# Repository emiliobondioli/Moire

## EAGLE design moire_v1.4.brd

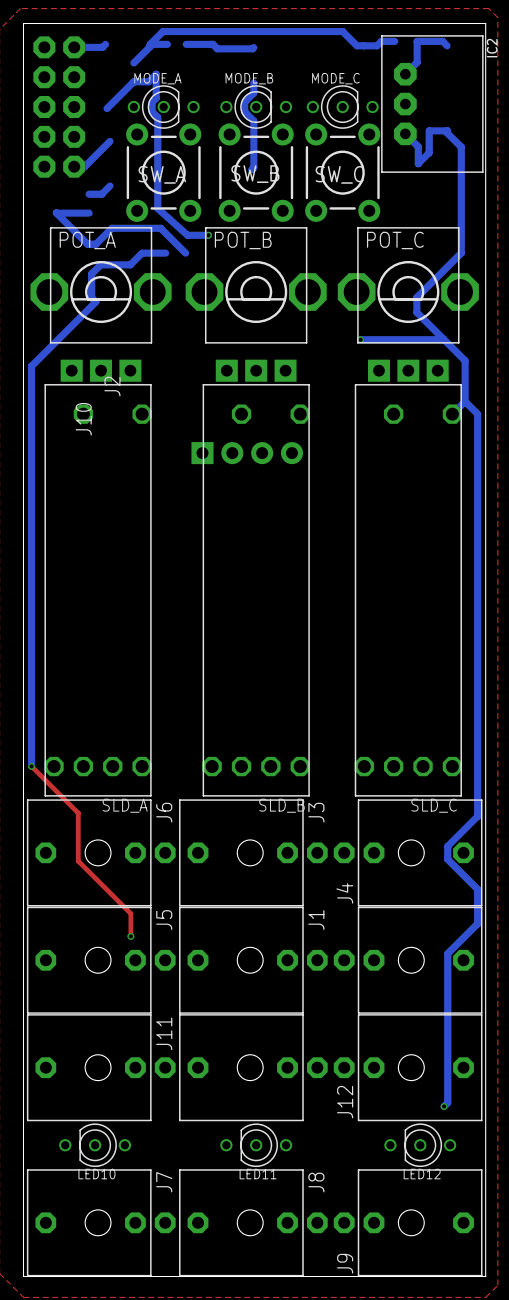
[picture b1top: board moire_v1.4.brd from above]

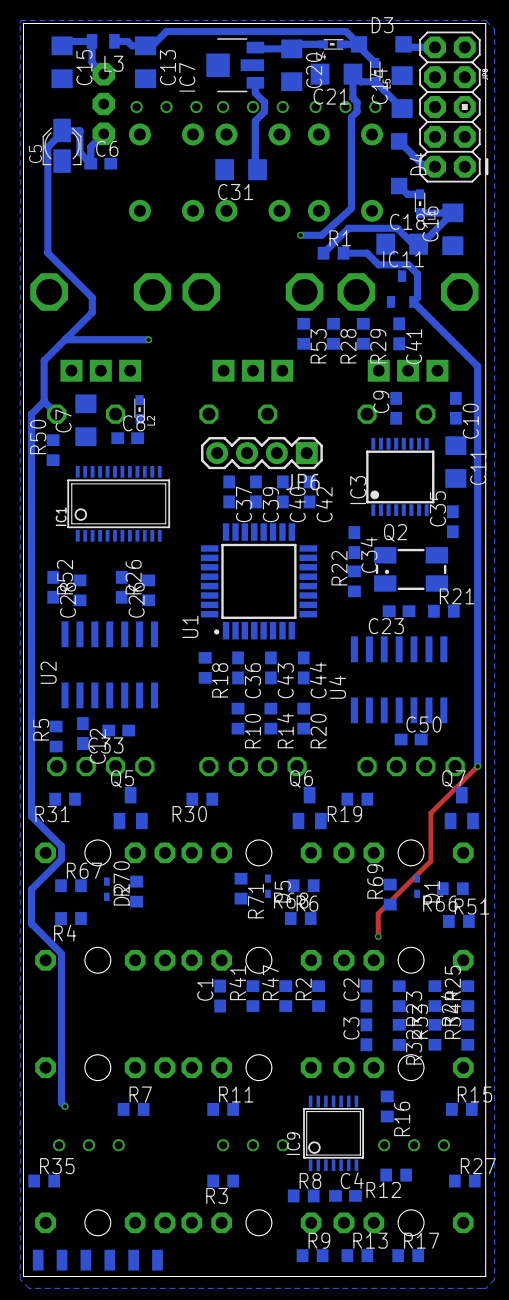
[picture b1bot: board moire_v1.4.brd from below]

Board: 2 copper layers, 39.4 x 106.7 mm, 135 parts (107 on the bottom side), 102 nets.

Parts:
C1, C2, C3: 100p; C0603
C4, C6, C8, C9, C10, C23, C33, C36, C37, C39, C43, C50: 100n; C0603
C5: 10u; PANASONIC_A
C7, C11, C13, C14, C15, C16, C18, C20, C21, C31: 22u; C1206
C12, C26, C28: 2.2n; C0603
C34, C35: 20p; C0603
C40, C41, C42, C44: 1u; C0603
D1, D2, D5: 1N4148; SOD523
D3, D4: 1N5819HW; SOD123
IC1: TLC59281DBQ; TSSOP24_0635
IC2: R-78E3.3-0.5; WE78
IC3: 4051PW; TSSOP16_065
IC7: LD2981ABU33; SOT89
IC9: LM324PW; TSSOP14_065
IC11: LM4040B25; DBZ_R-PDSO-G3
J1, J2, J3, J4, J5, J6, J7, J8, J9, J10, J11, J12: PJ301_THONKICONN6; WQP_PJ_301M6
JP6: 1X04
JP8: M05X2PTH; 2X5-PTH
L1, L2, L4, L5: 0603
L3: 33u; L2012C
LED10, LED11, LED12: SSL-LX3059IGW-CA; LED-BICOLOR-THROUGHHOLE-LUMEX
MODE_A: SSL-LX3059IGW-CA; LED-BICOLOR-THROUGHHOLE-LUMEX
MODE_B: SSL-LX3059IGW-CA; LED-BICOLOR-THROUGHHOLE-LUMEX
MODE_C: SSL-LX3059IGW-CA; LED-BICOLOR-THROUGHHOLE-LUMEX
POT_A: 10kB; ALPS_POT_VERTICAL
POT_B: 10kB; ALPS_POT_VERTICAL
POT_C: 10kB; ALPS_POT_VERTICAL
Q2: 8MHz; CTS406
Q5, Q6, Q7: MMBT3904; SOT23-BEC
R1, R10, R14, R18, R20, R50: 10k; R0603
R2, R25, R28, R29, R34, R53: 30k; R0603
R3, R7, R11, R15, R27, R35: 1.0k; R0603
R4, R6, R8, R12, R16, R23, R32, R41, R51, R66, R67, R68, R69, R70, R71: 100k; R0603
R5, R24, R26, R33, R47, R52: 20k; R0603
R9, R13, R17: 69.8k; R0603
R19, R30, R31: 15k; R0603
R21, R22: 100; R0603
SLD_A: 20kB; BOURNS_SLIDER
SLD_B: 20kB; BOURNS_SLIDER
SLD_C: 20kB; BOURNS_SLIDER
SW_A: TACTILE-PTH
SW_B: TACTILE-PTH
SW_C: TACTILE-PTH
U1: STM32F303K8T6; QFP80P900X900X160-32N
U2: MCP6004; SO14
U4: TL074; SO14
U$1: 1X6-SMD-TESTPAD; 6X1-SMD-TESTPAD

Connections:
+3V3: C5.+, C6.1, C37.1, C39.1, C40.1, C42.1, IC2.3, L2.2, LED10.A, LED11.A, LED12.A, MODE_A.A, MODE_B.A, MODE_C.A, R18.1, SLD_A.B, SLD_B.B, SLD_C.B, U1.1, U1.17, U$1.3
+3V3_A: C9.1, C10.1, C11.1, C31.1, C33.1, C43.1, C44.1, IC3.16, IC7.1, POT_A.P$1, POT_B.P$1, POT_C.P$1, SLD_A.3, SLD_B.3, SLD_C.3, U1.5, U2.4, U$1.4
+12V: D3.A, JP8.9, JP8.10
-12V: D4.C, JP8.1, JP8.2
ADC_TIME_SHAPE: IC3.3, U1.9
AREF_-2.5: C41.1, IC11.2, R1.2, R2.2, R25.2, R28.2, R29.2, R34.2, R53.2, U$1.5
A_ADC: R47.2, U1.10
A_CV: C12.2, R5.1, U1.6, U2.1
A_GATE: R10.2, U1.20
A_TRIG: Q5.C, U1.25
A_TRIG_IN: J4.P3, R67.1
B_ADC: R24.2, U1.11
B_CV: C26.2, R26.1, U1.7, U2.8
B_CV_IN: J1.P3, R6.2
B_GATE: R14.2, U1.21
B_TRIG: Q6.C, U1.14
B_TRIG_IN: J3.P3, R68.1
C_ADC: R33.2, U1.12
C_CV: C28.2, R52.1, U1.8, U2.14
C_GATE: R20.2, U1.22
C_TRIG: Q7.C, U1.15
C_TRIG_IN: J6.P3, R66.1
GND: C4.2, C5.-, C6.2, C7.2, C8.2, C9.2, C10.2, C11.2, C13.2, C14.2, C15.2, C16.1, C18.1, C20.2, C21.2, C23.1, C31.2, C33.2, C34.1, C35.1, C36.2, C37.2, C39.2, C40.2, C41.2, C42.2, C43.2, C44.2, C50.2, D1.A, D2.A, D5.A, IC1.1, IC1.21, IC2.2, IC3.6, IC3.7, IC3.8, IC7.2, IC9.11, IC9.12, IC11.1, J1.P1, J1.P2, J2.P1, J2.P2, J3.P1, J3.P2, J4.P1, J4.P2, J5.P1, J5.P2, J6.P1, J6.P2, J7.P1, J8.P1, J9.P1, J10.P1, J11.P1, J12.P1, JP6.1, JP8.3, JP8.4, JP8.5, JP8.6, JP8.7, JP8.8, POT_A.P$3, POT_B.P$3, POT_C.P$3, Q2.2, Q2.4, Q5.E, Q6.E, Q7.E, R9.2, R13.2, R17.2, R50.2, R69.1, R70.1, R71.1, SLD_A.1, SLD_B.1, SLD_C.1, SW_A.1, SW_A.2, SW_B.1, SW_B.2, SW_C.1, SW_C.2, U1.16, U1.31, U1.32, U2.3, U2.5, U2.10, U2.11, U2.12, U4.3, U4.5, U4.10, U4.12, U$1.6
LEDS_SCK: IC1.3, U1.26
LEDS_SIN: IC1.2, U1.28
unnamed: R31.1, SLD_C.E
unnamed: J12.P3, R7.1
unnamed: D4.A, L1.2
unnamed: C13.1, D3.C, L3.1, L4.2, L5.2
unnamed: C20.1, IC7.3, L4.1
unnamed: IC9.13, IC9.14
unnamed: J8.P3, R3.1, R23.1
unnamed: C2.1, R23.2, R24.1, R25.1, U4.6
unnamed: R21.1, U1.2
unnamed: R22.1, U1.3
unnamed: C35.2, Q2.3, R21.2
unnamed: C34.2, Q2.1, R22.2
unnamed: J10.P3, R11.1
unnamed: U4.13, U4.14
unnamed: C2.2, R3.2, U4.7
unnamed: IC9.1, R7.2, R8.1
unnamed: J7.P3, R27.1, R32.1
unnamed: C3.1, R32.2, R33.1, R34.1, U4.9
unnamed: C3.2, R27.2, U4.8
unnamed: J11.P3, R15.1
unnamed: J5.P3, R51.2
unnamed: J2.P3, R4.2
unnamed: IC9.3, R8.2, R9.1
unnamed: IC9.2, R10.1
unnamed: IC9.7, R11.2, R12.1
unnamed: IC9.5, R12.2, R13.1
unnamed: IC9.6, R14.1
unnamed: IC9.8, R15.2, R16.1
unnamed: IC1.11, MODE_B.GREEN_C
unnamed: IC1.10, MODE_A.RED_C
unnamed: IC1.12, MODE_B.RED_C
unnamed: IC1.7, MODE_C.RED_C
unnamed: IC1.8, MODE_C.GREEN_C
unnamed: IC1.15, LED11.RED_C
unnamed: IC1.16, LED11.GREEN_C
unnamed: IC1.13, LED10.GREEN_C
unnamed: IC1.17, LED12.RED_C
unnamed: D1.C, Q7.B, R66.2, R69.2
unnamed: IC1.18, LED12.GREEN_C
unnamed: IC1.14, LED10.RED_C
unnamed: C7.1, C8.1, IC1.24, L2.1
unnamed: IC1.19, R19.2
unnamed: IC1.20, R30.2
unnamed: IC1.6, R31.2
unnamed: IC3.1, SLD_A.2
unnamed: R30.1, SLD_B.E
unnamed: R19.1, SLD_A.E
unnamed: IC3.2, POT_B.P$2
unnamed: IC3.12, POT_A.P$2
unnamed: IC3.13, POT_C.P$2
unnamed: IC3.14, SLD_C.2
unnamed: IC3.15, SLD_B.2
unnamed: C12.1, R4.1, R5.2, R29.1, U2.2
unnamed: C26.1, R6.1, R26.2, R28.1, U2.9
unnamed: C28.1, R51.1, R52.2, R53.1, U2.13
unnamed: IC9.10, R16.2, R17.1
unnamed: D5.C, Q6.B, R68.2, R71.2
unnamed: IC9.9, R20.1
unnamed: D2.C, Q5.B, R67.2, R70.2
unnamed: C15.1, IC2.1, L3.2
unnamed: IC1.23, R50.1
unnamed: J9.P3, R35.1, R41.1
unnamed: C1.1, R2.1, R41.2, R47.1, U4.2
unnamed: C1.2, R35.2, U4.1
unnamed: IC1.9, MODE_A.GREEN_C
N_U: U2.6, U2.7
POTS_ADDR_A: IC3.11, U1.13
POTS_ADDR_B: IC3.10, U1.18
POTS_ADDR_C: IC3.9, U1.19
RESET: C36.1, JP6.4, R18.2, U1.4
SWCLK: JP6.3, U1.24
SWDIO: JP6.2, U1.23
SW_MODE_A: SW_A.3, SW_A.4, U1.27
SW_MODE_B: SW_B.3, SW_B.4, U1.29
SW_MODE_C: SW_C.3, SW_C.4, U1.30
VCC: C4.1, C14.1, C21.1, C50.1, IC9.4, L5.1, U4.4, U$1.1
VEE: C16.2, C18.2, C23.2, L1.1, R1.1, U4.11, U$1.2

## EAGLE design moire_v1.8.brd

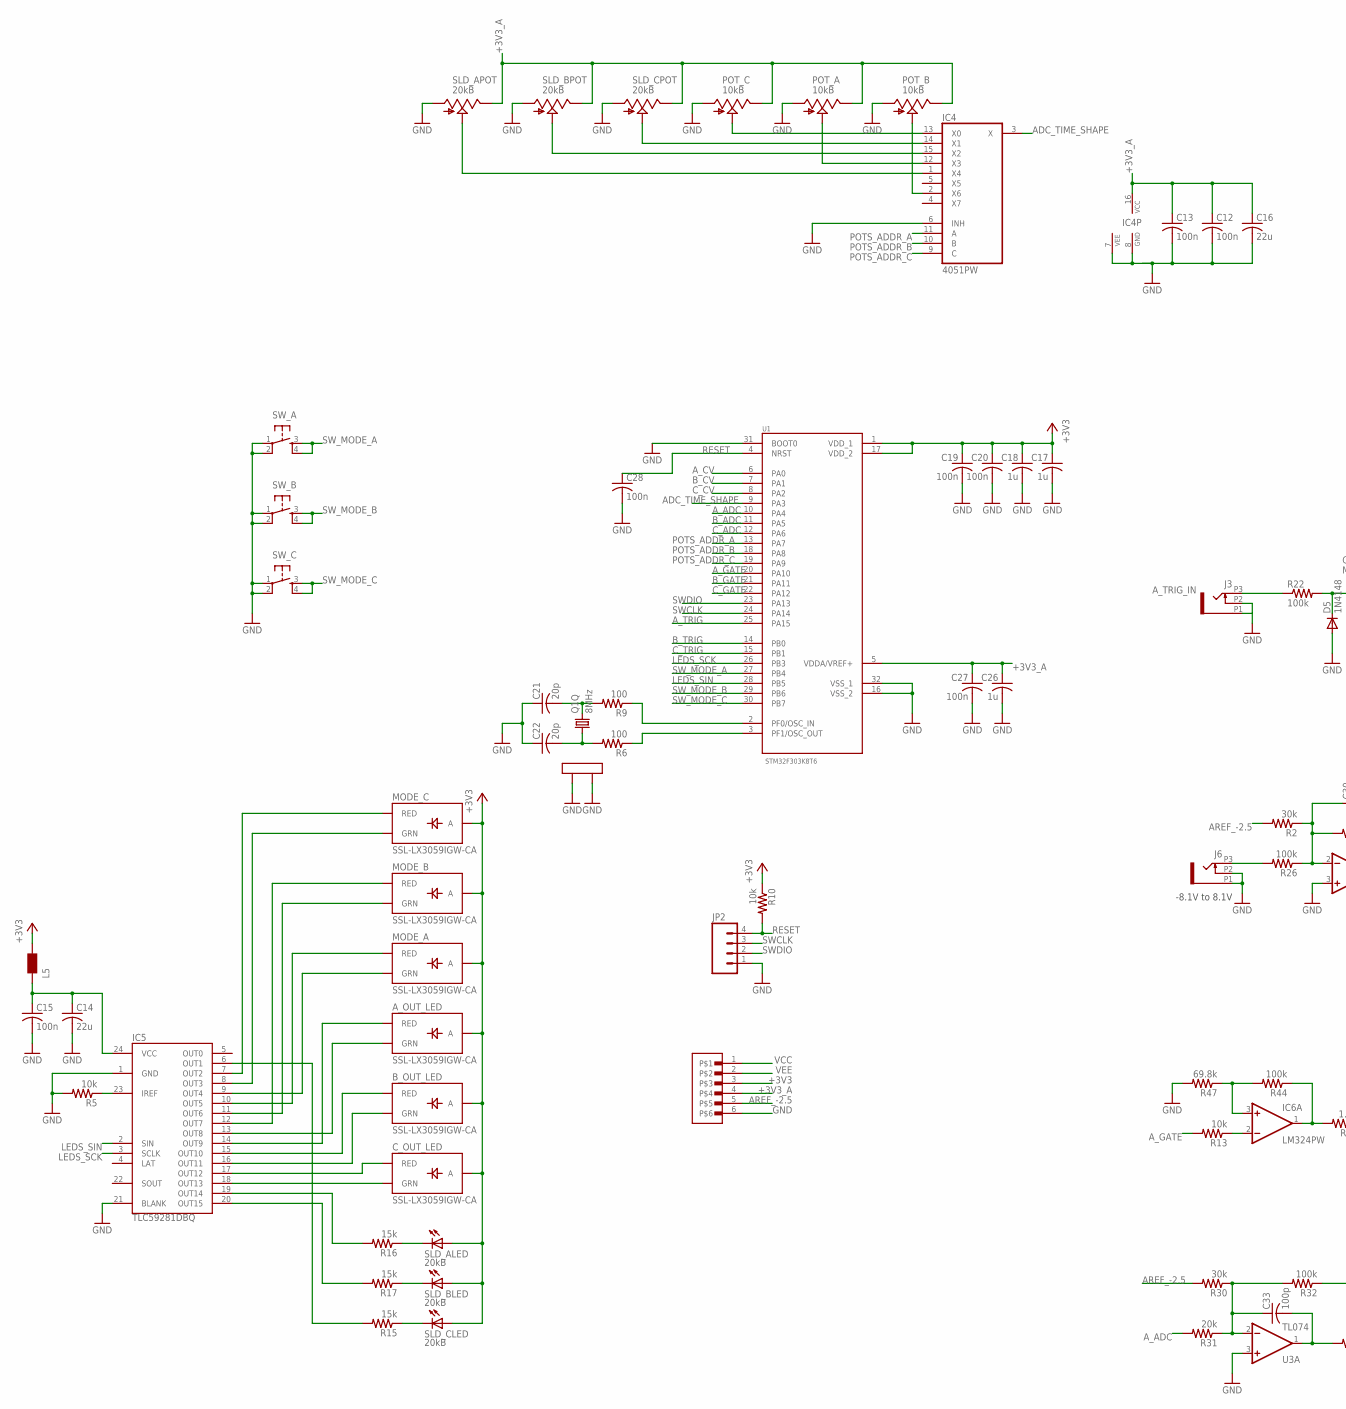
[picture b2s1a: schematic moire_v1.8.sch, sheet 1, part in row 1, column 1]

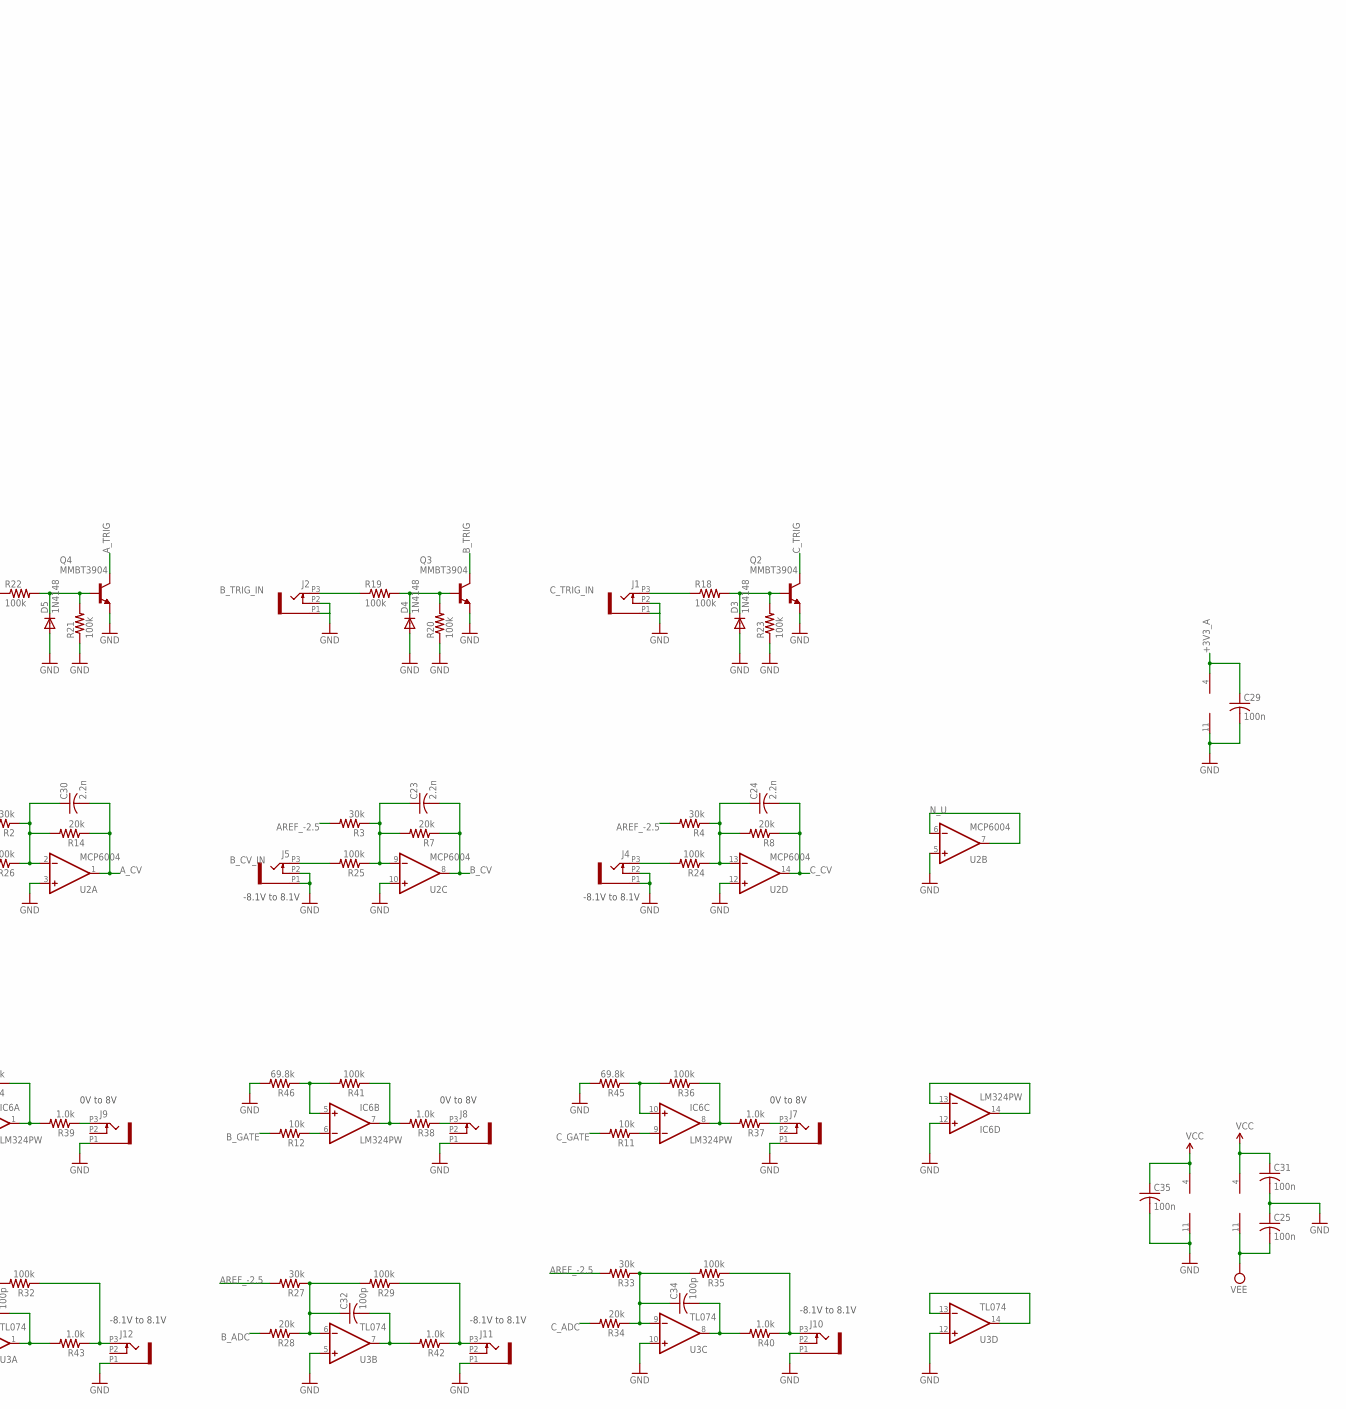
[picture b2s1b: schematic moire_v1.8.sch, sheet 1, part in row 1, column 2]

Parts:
A_OUT_LED: SSL-LX3059IGW-CA; LED-BICOLOR-THROUGHHOLE-LUMEX
B_OUT_LED: SSL-LX3059IGW-CA; LED-BICOLOR-THROUGHHOLE-LUMEX
C12, C13, C15, C19, C20, C25, C27, C28, C29, C31, C35: 100n; RCL_C0603
C14, C16: 22u; RCL_C1206
C17, C18, C26: 1u; RCL_C0603
C21, C22: 20p; RCL_C0603
C23, C24, C30: 2.2n; RCL_C0603
C32, C33, C34: 100p; RCL_C0603
C_OUT_LED: SSL-LX3059IGW-CA; LED-BICOLOR-THROUGHHOLE-LUMEX
D3, D4, D5: 1N4148; DIODE_SOD523
IC4: 4051PW; TSSOP16_065
IC5: TLC59281DBQ; TSSOP24_0635
IC6: LM324PW; TSSOP14_065
J1, J2, J3, J4, J5, J6, J7, J8, J9, J10, J11, J12: PJ301_THONKICONN6; WQP_PJ_301M6
JP2: M04PTH; 1X04
L5: WE-CBF_0603; 0603
MODE_A: SSL-LX3059IGW-CA; LED-BICOLOR-THROUGHHOLE-LUMEX
MODE_B: SSL-LX3059IGW-CA; LED-BICOLOR-THROUGHHOLE-LUMEX
MODE_C: SSL-LX3059IGW-CA; LED-BICOLOR-THROUGHHOLE-LUMEX
POT_A: 10kB; ALPS_POT_VERTICAL
POT_B: 10kB; ALPS_POT_VERTICAL
POT_C: 10kB; ALPS_POT_VERTICAL
Q1: 8MHz; CTS406
Q2, Q3, Q4: MMBT3904; SOT23-BEC
R2, R3, R4, R27, R30, R33: 30k; RCL_R0603
R5, R10, R11, R12, R13: 10k; RCL_R0603
R6, R9: 100; RCL_R0603
R7, R8, R14, R28, R31, R34: 20k; RCL_R0603
R15, R16, R17: 15k; RCL_R0603
R18, R19, R20, R21, R22, R23, R24, R25, R26, R29, R32, R35, R36, R41, R44: 100k; RCL_R0603
R37, R38, R39, R40, R42, R43: 1.0k; RCL_R0603
R45, R46, R47: 69.8k; RCL_R0603
SLD_A: 20kB; BOURNS_SLIDER
SLD_B: 20kB; BOURNS_SLIDER
SLD_C: 20kB; BOURNS_SLIDER
SW_A: TAC_SWITCHPTH; TACTILE-PTH
SW_B: TAC_SWITCHPTH; TACTILE-PTH
SW_C: TAC_SWITCHPTH; TACTILE-PTH
U1: STM32F303K8T6; QFP80P900X900X160-32N
U2: MCP6004; SO14
U3: TL074; SO14
U$1: 1X6-SMD-TESTPAD; 6X1-SMD-TESTPAD

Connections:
+3V3: A_OUT_LED.A, B_OUT_LED.A, C17.1, C18.1, C19.1, C20.1, C_OUT_LED.A, L5.2, MODE_A.A, MODE_B.A, MODE_C.A, R10.1, SLD_A.B (A), SLD_B.B (A), SLD_C.B (A), U1.1 (VDD_1), U1.17 (VDD_2), U$1.3; also elsewhere on the board
+3V3_A: C12.1, C13.1, C16.1, C26.1, C27.1, C29.1, IC4.16 (VCC), POT_A.P$1 (E), POT_B.P$1 (E), POT_C.P$1 (E), SLD_A.3 (E), SLD_B.3 (E), SLD_C.3 (E), U1.5 (VDDA/VREF+), U2.4 (V+), U$1.4; also elsewhere on the board
ADC_TIME_SHAPE: IC4.3 (X), U1.9 (PA3)
AREF_-2.5: R2.2, R3.2, R4.2, R27.2, R30.2, R33.2, U$1.5; also elsewhere on the board
A_ADC: R31.2, U1.10 (PA4)
A_CV: C30.2, R14.1, U1.6 (PA0), U2.1 (OUT)
A_GATE: R13.2, U1.20 (PA10)
A_TRIG: Q4.C, U1.25 (PA15)
A_TRIG_IN: J3.P3 (3), R22.1
B_ADC: R28.2, U1.11 (PA5)
B_CV: C23.2, R7.1, U1.7 (PA1), U2.8 (OUT)
B_CV_IN: J5.P3 (3), R25.2
B_GATE: R12.2, U1.21 (PA11)
B_TRIG: Q3.C, U1.14 (PB0)
B_TRIG_IN: J2.P3 (3), R19.1
C_ADC: R34.2, U1.12 (PA6)
C_CV: C24.2, R8.1, U1.8 (PA2), U2.14 (OUT)
C_GATE: R11.2, U1.22 (PA12)
C_TRIG: Q2.C, U1.15 (PB1)
C_TRIG_IN: J1.P3 (3), R18.1
GND: C12.2, C13.2, C14.2, C15.2, C16.2, C17.2, C18.2, C19.2, C20.2, C21.1, C22.1, C25.1, C26.2, C27.2, C28.2, C29.2, C31.2, C35.2, D3.A, D4.A, D5.A, IC4.6 (INH), IC4.7 (VEE), IC4.8 (GND), IC5.1 (GND), IC5.21 (BLANK), IC6.11 (V-), IC6.12 (+IN), J1.P1 (1), J1.P2 (2), J2.P1 (1), J2.P2 (2), J3.P1 (1), J3.P2 (2), J4.P1 (1), J4.P2 (2), J5.P1 (1), J5.P2 (2), J6.P1 (1), J6.P2 (2), J7.P1 (1), J8.P1 (1), J9.P1 (1), J10.P1 (1), J11.P1 (1), J12.P1 (1), JP2.1, POT_A.P$3 (A), POT_B.P$3 (A), POT_C.P$3 (A), Q1.2 (LID1), Q1.4 (LID2), Q2.E, Q3.E, Q4.E, R5.2, R20.1, R21.1, R23.1, R45.2, R46.2, R47.2, SLD_A.1 (A), SLD_B.1 (A), SLD_C.1 (A), SW_A.1, SW_A.2, SW_B.1, SW_B.2, SW_C.1, SW_C.2, U1.16 (VSS_2), U1.31 (BOOT0), U1.32 (VSS_1), U2.3 (+IN), U2.5 (+IN), U2.10 (+IN), U2.11 (V-), U2.12 (+IN), U3.3 (+IN), U3.5 (+IN), U3.10 (+IN), U3.12 (+IN), U$1.6; also elsewhere on the board
LEDS_SCK: IC5.3 (SCLK), U1.26 (PB3)
LEDS_SIN: IC5.2 (SIN), U1.28 (PB5)
unnamed: R15.1, SLD_C.E (C)
unnamed: J9.P3 (3), R39.1
unnamed: IC6.13 (-IN), IC6.14 (OUT)
unnamed: J11.P3 (3), R29.1, R42.1
unnamed: C32.1, R27.1, R28.1, R29.2, U3.6 (-IN)
unnamed: R9.1, U1.2 (PF0/OSC_IN)
unnamed: R6.1, U1.3 (PF1/OSC_OUT)
unnamed: C21.2, Q1.3 (2), R9.2
unnamed: C22.2, Q1.1, R6.2
unnamed: J8.P3 (3), R38.1
unnamed: U3.13 (-IN), U3.14 (OUT)
unnamed: C32.2, R42.2, U3.7 (OUT)
unnamed: IC6.1 (OUT), R39.2, R44.1
unnamed: J10.P3 (3), R35.1, R40.1
unnamed: C34.1, R33.1, R34.1, R35.2, U3.9 (-IN)
unnamed: C34.2, R40.2, U3.8 (OUT)
unnamed: J7.P3 (3), R37.1
unnamed: J4.P3 (3), R24.2
unnamed: J6.P3 (3), R26.2
unnamed: IC6.3 (+IN), R44.2, R47.1
unnamed: IC6.2 (-IN), R13.1
unnamed: IC6.7 (OUT), R38.2, R41.1
unnamed: IC6.5 (+IN), R41.2, R46.1
unnamed: IC6.6 (-IN), R12.1
unnamed: IC6.8 (OUT), R36.1, R37.2
unnamed: IC5.11 (OUT6), MODE_B.GREEN_C (GRN)
unnamed: IC5.10 (OUT5), MODE_A.RED_C (RED)
unnamed: IC5.12 (OUT7), MODE_B.RED_C (RED)
unnamed: IC5.7 (OUT2), MODE_C.RED_C (RED)
unnamed: IC5.8 (OUT3), MODE_C.GREEN_C (GRN)
unnamed: B_OUT_LED.RED_C (RED), IC5.15 (OUT10)
unnamed: B_OUT_LED.GREEN_C (GRN), IC5.16 (OUT11)
unnamed: A_OUT_LED.GREEN_C (GRN), IC5.13 (OUT8)
unnamed: C_OUT_LED.RED_C (RED), IC5.17 (OUT12)
unnamed: D3.C, Q2.B, R18.2, R23.2
unnamed: C_OUT_LED.GREEN_C (GRN), IC5.18 (OUT13)
unnamed: A_OUT_LED.RED_C (RED), IC5.14 (OUT9)
unnamed: C14.1, C15.1, IC5.24 (VCC), L5.1
unnamed: IC5.19 (OUT14), R16.2
unnamed: IC5.20 (OUT15), R17.2
unnamed: IC5.6 (OUT1), R15.2
unnamed: IC4.1 (X4), SLD_A.2 (S)
unnamed: R17.1, SLD_B.E (C)
unnamed: R16.1, SLD_A.E (C)
unnamed: IC4.2 (X6), POT_B.P$2 (S)
unnamed: IC4.12 (X3), POT_A.P$2 (S)
unnamed: IC4.13 (X0), POT_C.P$2 (S)
unnamed: IC4.14 (X1), SLD_C.2 (S)
unnamed: IC4.15 (X2), SLD_B.2 (S)
unnamed: C30.1, R2.1, R14.2, R26.1, U2.2 (-IN)
unnamed: C23.1, R3.1, R7.2, R25.1, U2.9 (-IN)
unnamed: C24.1, R4.1, R8.2, R24.1, U2.13 (-IN)
unnamed: IC6.10 (+IN), R36.2, R45.1
unnamed: D4.C, Q3.B, R19.2, R20.2
unnamed: IC6.9 (-IN), R11.1
unnamed: D5.C, Q4.B, R21.2, R22.2
unnamed: IC5.23 (IREF), R5.1
unnamed: J12.P3 (3), R32.1, R43.1
unnamed: C33.1, R30.1, R31.1, R32.2, U3.2 (-IN)
unnamed: C33.2, R43.2, U3.1 (OUT)
unnamed: IC5.9 (OUT4), MODE_A.GREEN_C (GRN)
N_U: U2.6 (-IN), U2.7 (OUT)
POTS_ADDR_A: IC4.11 (A), U1.13 (PA7)
POTS_ADDR_B: IC4.10 (B), U1.18 (PA8)
POTS_ADDR_C: IC4.9 (C), U1.19 (PA9)
RESET: C28.1, JP2.4, R10.2, U1.4 (NRST)
SWCLK: JP2.3, U1.24 (PA14)
SWDIO: JP2.2, U1.23 (PA13)
SW_MODE_A: SW_A.3, SW_A.4, U1.27 (PB4)
SW_MODE_B: SW_B.3, SW_B.4, U1.29 (PB6)
SW_MODE_C: SW_C.3, SW_C.4, U1.30 (PB7)
VCC: C31.1, C35.1, IC6.4 (V+), U3.4 (V+), U$1.1; also elsewhere on the board
VEE: C25.2, U3.11 (V-), U$1.2; also elsewhere on the board

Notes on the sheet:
-8.1V to 8.1V
0V to 8V

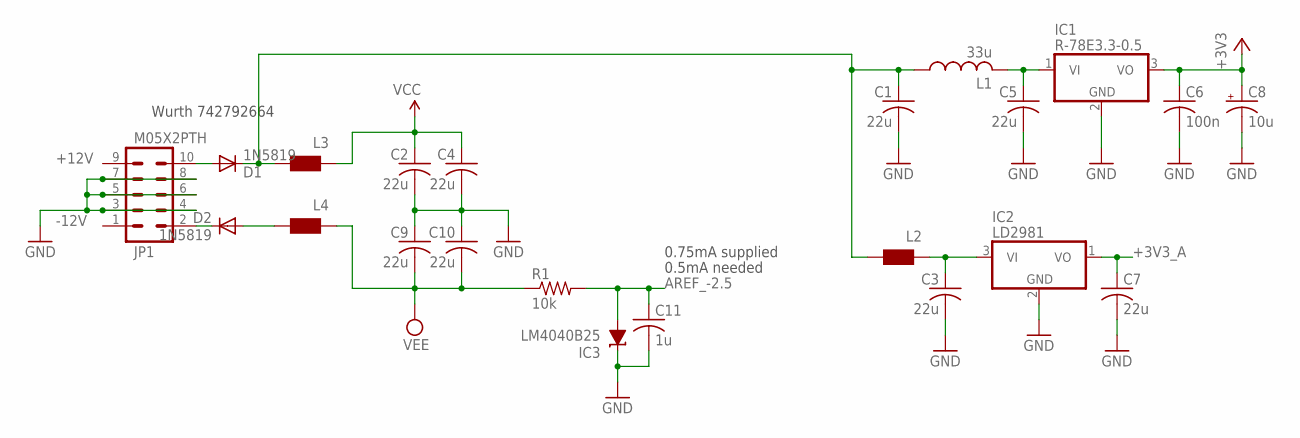
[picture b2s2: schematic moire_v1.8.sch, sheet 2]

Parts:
C1, C2, C3, C4, C5, C7, C9, C10: 22u; RCL_C1206
C6: 100n; RCL_C0603
C8: 10u; RCL_PANASONIC_A
C11: 1u; RCL_C0603
D1, D2: 1N5819; DIODE_SOD123
IC1: R-78E3.3-0.5; WE78
IC2: LD2981; SOT89
IC3: LM4040B25; DBZ_R-PDSO-G3
JP1: M05X2PTH; 2X5-PTH
L1: 33u; L2012C
L2, L3, L4: WE-CBF_0603; 0603
R1: 10k; RCL_R0603

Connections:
+3V3: C6.1, C8.+, IC1.3 (VO); also elsewhere on the board
+3V3_A: C7.1, IC2.1 (VO); also elsewhere on the board
+12V: D1.A, JP1.9, JP1.10
-12V: D2.C, JP1.1, JP1.2
AREF_-2.5: C11.1, IC3.2 (A), R1.2; also elsewhere on the board
GND: C1.2, C2.2, C3.2, C4.2, C5.2, C6.2, C7.2, C8.-, C9.1, C10.1, C11.2, IC1.2 (GND), IC2.2 (GND), IC3.1 (C), JP1.3, JP1.4, JP1.5, JP1.6, JP1.7, JP1.8; also elsewhere on the board
unnamed: D2.A, L4.2
unnamed: C1.1, D1.C, L1.1, L2.2, L3.2
unnamed: C3.1, IC2.3 (VI), L2.1
unnamed: C5.1, IC1.1 (VI), L1.2
VCC: C2.1, C4.1, L3.1; also elsewhere on the board
VEE: C9.2, C10.2, L4.1, R1.1; also elsewhere on the board

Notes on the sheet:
0.5mA needed
Wurth 742792664
0.75mA supplied

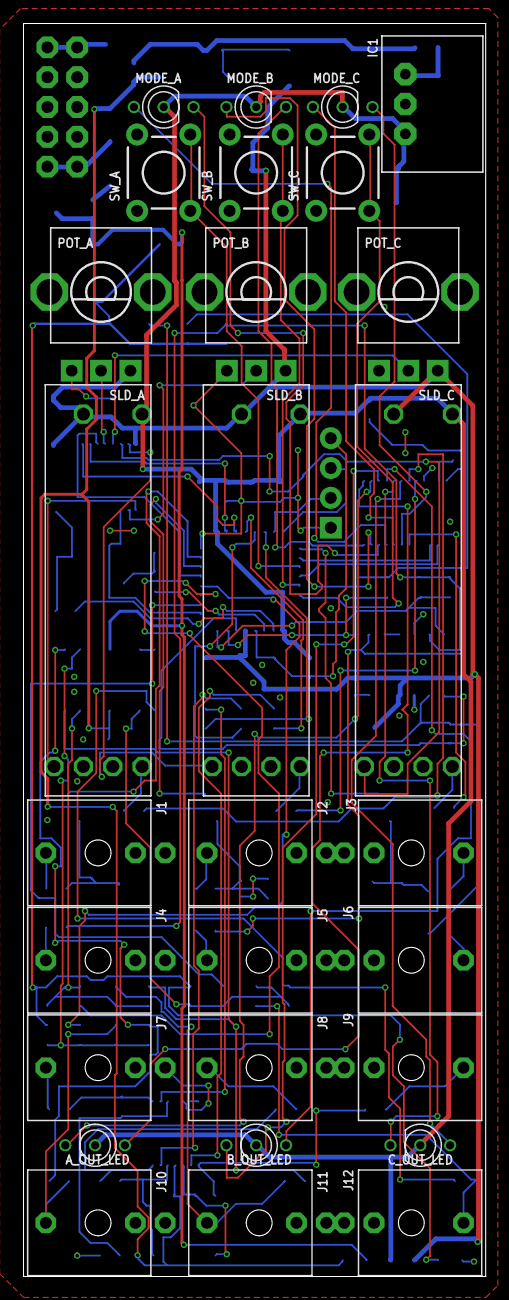
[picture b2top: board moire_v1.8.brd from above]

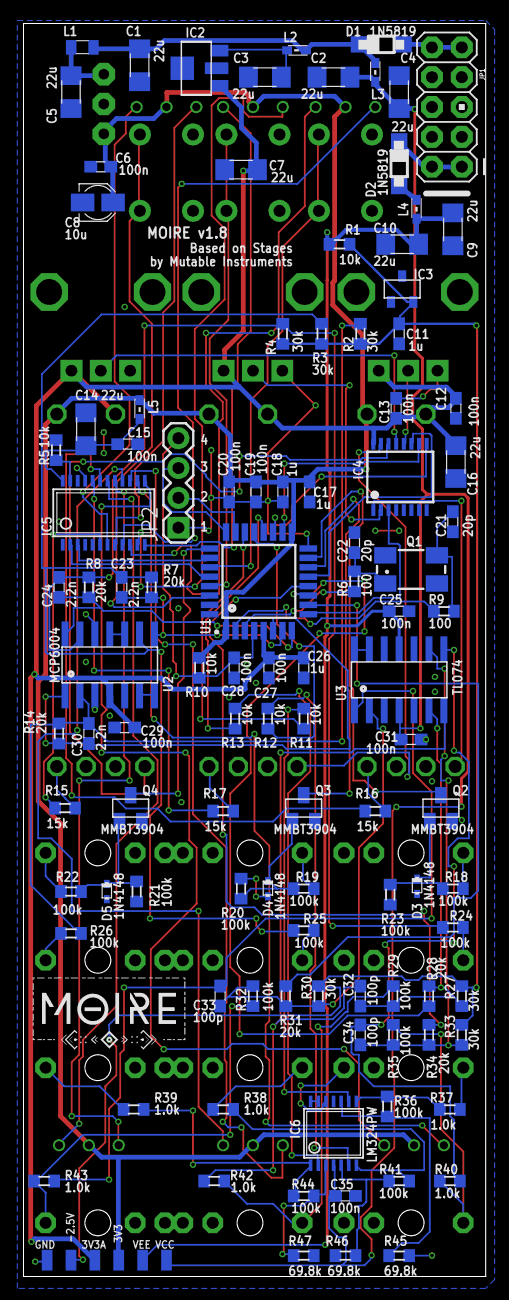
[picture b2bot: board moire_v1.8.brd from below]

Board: 2 copper layers, 39.4 x 106.7 mm, 135 parts (107 on the bottom side), 102 nets.
